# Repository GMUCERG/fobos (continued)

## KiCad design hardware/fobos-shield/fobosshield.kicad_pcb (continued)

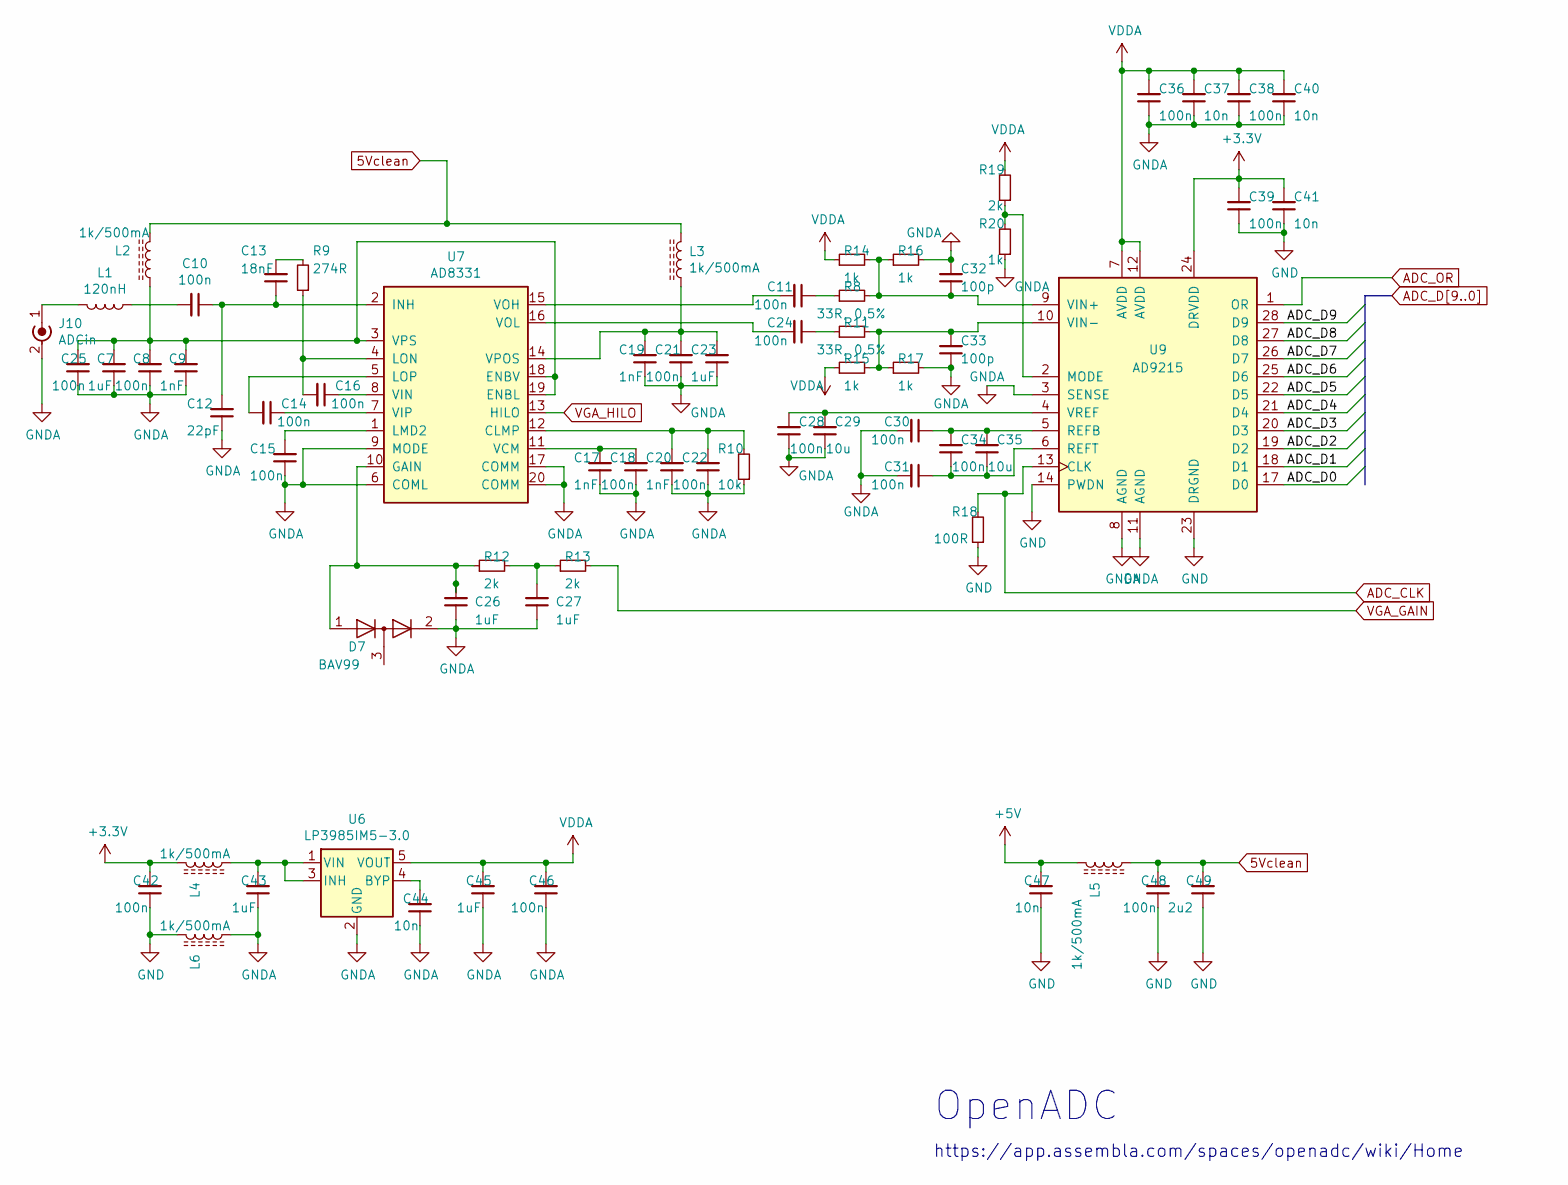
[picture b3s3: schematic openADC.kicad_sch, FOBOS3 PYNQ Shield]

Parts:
C7, C23, C26, C27, C43, C45: 1uF; C_0603_1608Metric
C8, C10, C11, C14, C15, C16, C18, C21, C22, C24, C25, C28, C30, C31, C34, C36, C38, C39, C42, C46, C48: 100n; C_0603_1608Metric
C9, C17, C19, C20: 1nF; C_0603_1608Metric
C12: 22pF; C_0603_1608Metric
C13: 18nF; C_0603_1608Metric
C29, C35: 10u; C_0603_1608Metric
C32, C33: 100p; C_0603_1608Metric
C37, C40, C41, C44, C47: 10n; C_0603_1608Metric
C49: 2u2; C_0603_1608Metric
D7: BAV99; SOT-23
J10: ADCin; SMA-JOHNSON-142-0701-801
L1: 120nH; L_0402_1005Metric
L2, L3, L4, L5, L6: 1k/500mA; L_0603_1608Metric
R8, R11: 33R, 0.5%; R_0603_1608Metric
R9: 274R; R_0603_1608Metric
R10: 10k; R_0603_1608Metric
R12, R13, R19: 2k; R_0603_1608Metric
R14, R15, R16, R17, R20: 1k; R_0603_1608Metric
R18: 100R; R_0603_1608Metric
U6: LP3985IM5-3.0; TSOT-23-5
U7: AD8331; QSOP-20_3.9x8.7mm_P0.635mm
U9: AD9215; TSSOP-28_4.4x9.7mm_P0.65mm

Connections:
5Vclean: C48.2, C49.2, L2.2, L3.2, L5.1
ADC_CLK: R18.2, U9.13 (CLK); also elsewhere on the board
ADC_D0: U9.17 (D0); also elsewhere on the board
ADC_D1: U9.18 (D1); also elsewhere on the board
ADC_D2: U9.19 (D2); also elsewhere on the board
ADC_D3: U9.20 (D3); also elsewhere on the board
ADC_D4: U9.21 (D4); also elsewhere on the board
ADC_D5: U9.22 (D5); also elsewhere on the board
ADC_D6: U9.25 (D6); also elsewhere on the board
ADC_D7: U9.26 (D7); also elsewhere on the board
ADC_D8: U9.27 (D8); also elsewhere on the board
ADC_D9: U9.28 (D9); also elsewhere on the board
ADC_OR: U9.1 (OR); also elsewhere on the board
GND: C39.1, C41.1, C42.1, C47.1, C48.1, C49.1, L6.2, R18.1, U9.14 (PWDN), U9.23 (DRGND); also elsewhere on the board
GNDA: C7.1, C8.1, C9.1, C12.1, C15.1, C17.1, C18.1, C19.1, C20.1, C21.1, C22.1, C23.1, C25.1, C26.1, C27.1, C28.1, C29.1, C30.2, C31.2, C32.2, C33.1, C36.1, C37.1, C38.1, C40.1, C43.1, C44.1, C45.1, C46.1, D7.2 (A), J10.2 (Ext), L6.1, R10.1, R16.2, R17.2, R20.1, U6.2 (GND), U7.6 (COML), U7.9 (MODE), U7.17 (COMM), U7.20 (COMM), U9.3 (SENSE), U9.8 (AGND), U9.11 (AGND)
unnamed: C10.1, C12.2, C13.1, U7.2 (INH)
unnamed: C10.2, L1.1
unnamed: C11.1, R8.1
unnamed: C11.2, U7.15 (VOH)
unnamed: C13.2, R9.2
unnamed: C14.1, U7.7 (VIP)
unnamed: C14.2, U7.5 (LOP)
unnamed: C15.2, U7.1 (LMD2)
unnamed: C16.1, U7.8 (VIN)
unnamed: C16.2, R9.1, U7.4 (LON)
unnamed: C17.2, C18.2, U7.11 (VCM)
unnamed: C19.2, C21.2, C23.2, L3.1, U7.14 (VPOS)
unnamed: C20.2, C22.2, R10.2, U7.12 (CLMP)
unnamed: C24.1, R11.1
unnamed: C24.2, U7.16 (VOL)
unnamed: C7.2, C8.2, C9.2, C25.2, L2.1, U7.3 (VPS), U7.18 (ENBV), U7.19 (ENBL)
unnamed: C26.2, D7.1 (K), R12.1, U7.10 (GAIN)
unnamed: C27.2, R12.2, R13.1
unnamed: C28.2, C29.2, U9.4 (VREF)
unnamed: C30.1, C34.2, C35.2, U9.5 (REFB)
unnamed: C31.1, C34.1, C35.1, U9.6 (REFT)
unnamed: C32.1, R8.2, R14.2, R16.1, U9.9 (VIN+)
unnamed: C33.2, R11.2, R15.2, R17.1, U9.10 (VIN-)
unnamed: C43.2, L4.1, U6.1 (VIN), U6.3 (INH)
unnamed: C44.2, U6.4 (BYP)
unnamed: J10.1 (In), L1.2
unnamed: R19.1, R20.2, U9.2 (MODE)
VCC3V3: C39.2, C41.2, C42.2, L4.2, U9.24 (DRVDD); also elsewhere on the board
VCC5V0: C47.2, L5.2; also elsewhere on the board
VDDA: C36.2, C37.2, C38.2, C40.2, C45.2, C46.2, R14.1, R15.1, R19.2, U6.5 (VOUT), U9.7 (AVDD), U9.12 (AVDD)
VGA_GAIN: R13.2; also elsewhere on the board
VGA_HILO: U7.13 (HILO); also elsewhere on the board

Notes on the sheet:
OpenADC
https://app.assembla.com/spaces/openadc/wiki/Home

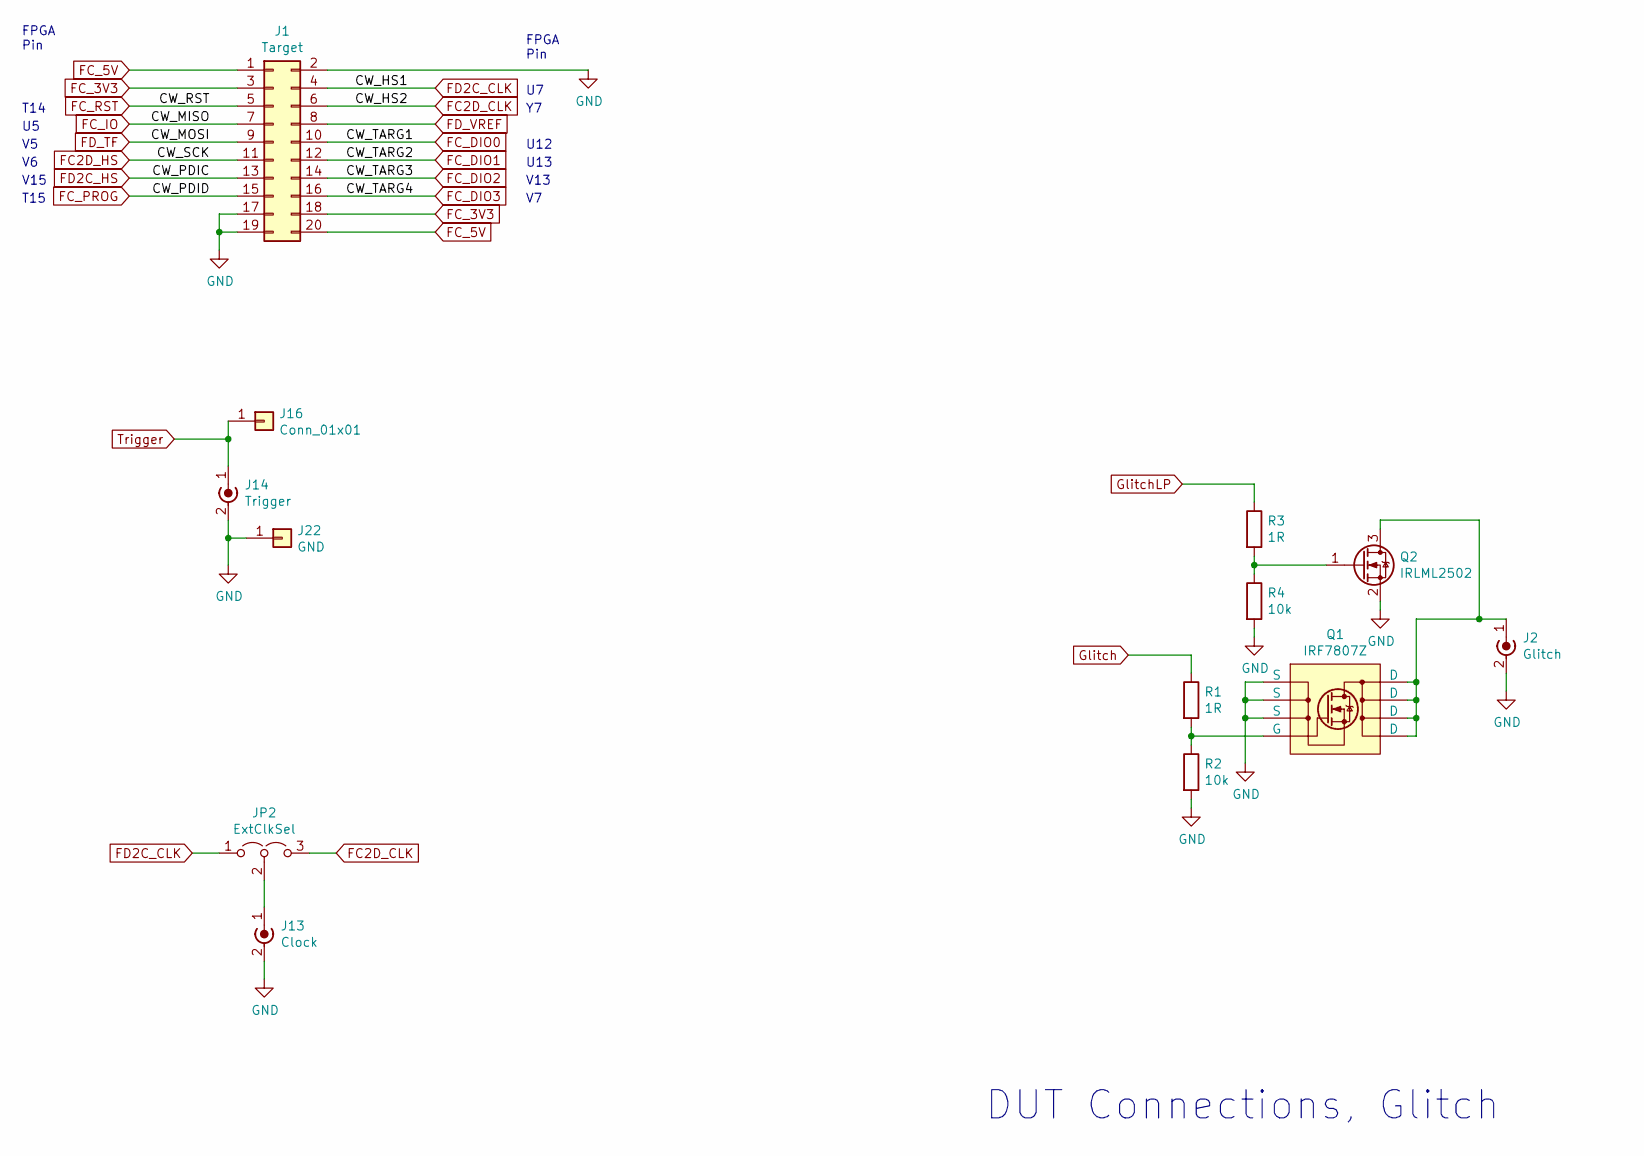
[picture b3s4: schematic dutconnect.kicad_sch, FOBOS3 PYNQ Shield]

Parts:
J1: Target; IDC-Header_2x10_P2.54mm_Horizontal
J2: Glitch; SMA-JOHNSON-142-0701-801
J13: Clock; SMA-JOHNSON-142-0701-801
J14: Trigger; SMA-JOHNSON-142-0701-801
J16: Conn_01x01; TestPoint_Loop_D2.60mm_Drill1.6mm_Beaded
J22: GND; TestPoint_Loop_D2.60mm_Drill1.6mm_Beaded
JP2: ExtClkSel; PinHeader_1x03_P2.54mm_Vertical
Q1: IRF7807Z; SOIC-8_3.9x4.9mm_P1.27mm
Q2: IRLML2502; SOT-23
R1, R3: 1R; R_0603_1608Metric
R2, R4: 10k; R_0603_1608Metric

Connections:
FC2D_CLK: J1.6, JP2.3 (B); also elsewhere on the board
FC2D_HS: J1.11; also elsewhere on the board
FC_3V3: J1.3, J1.18; also elsewhere on the board
FC_5V: J1.1, J1.20; also elsewhere on the board
FC_DIO0: J1.10; also elsewhere on the board
FC_DIO1: J1.12; also elsewhere on the board
FC_DIO2: J1.14; also elsewhere on the board
FC_DIO3: J1.16; also elsewhere on the board
FC_IO: J1.7; also elsewhere on the board
FC_PROG: J1.15; also elsewhere on the board
FC_RST: J1.5; also elsewhere on the board
FD2C_CLK: J1.4, JP2.1 (A); also elsewhere on the board
FD2C_HS: J1.13; also elsewhere on the board
FD_TF: J1.9; also elsewhere on the board
FD_VREF: J1.8
GND: J1.2, J1.17, J1.19, J2.2 (Ext), J13.2 (Ext), J14.2 (Ext), J22.1, Q1.1 (S), Q1.2 (S), Q1.3 (S), Q2.2 (S), R2.2, R4.2; also elsewhere on the board
Glitch: R1.1; also elsewhere on the board
GlitchLP: R3.1; also elsewhere on the board
unnamed: J2.1 (In), Q1.5 (D), Q1.6 (D), Q1.7 (D), Q1.8 (D), Q2.3 (D)
unnamed: J13.1 (In), JP2.2 (C)
unnamed: Q1.4 (G), R1.2, R2.1
unnamed: Q2.1 (G), R3.2, R4.1
Trigger: J14.1 (In), J16.1; also elsewhere on the board

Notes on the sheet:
V15
V13
T14
DUT Connections, Glitch
U12
T15
FPGA Pin
U13

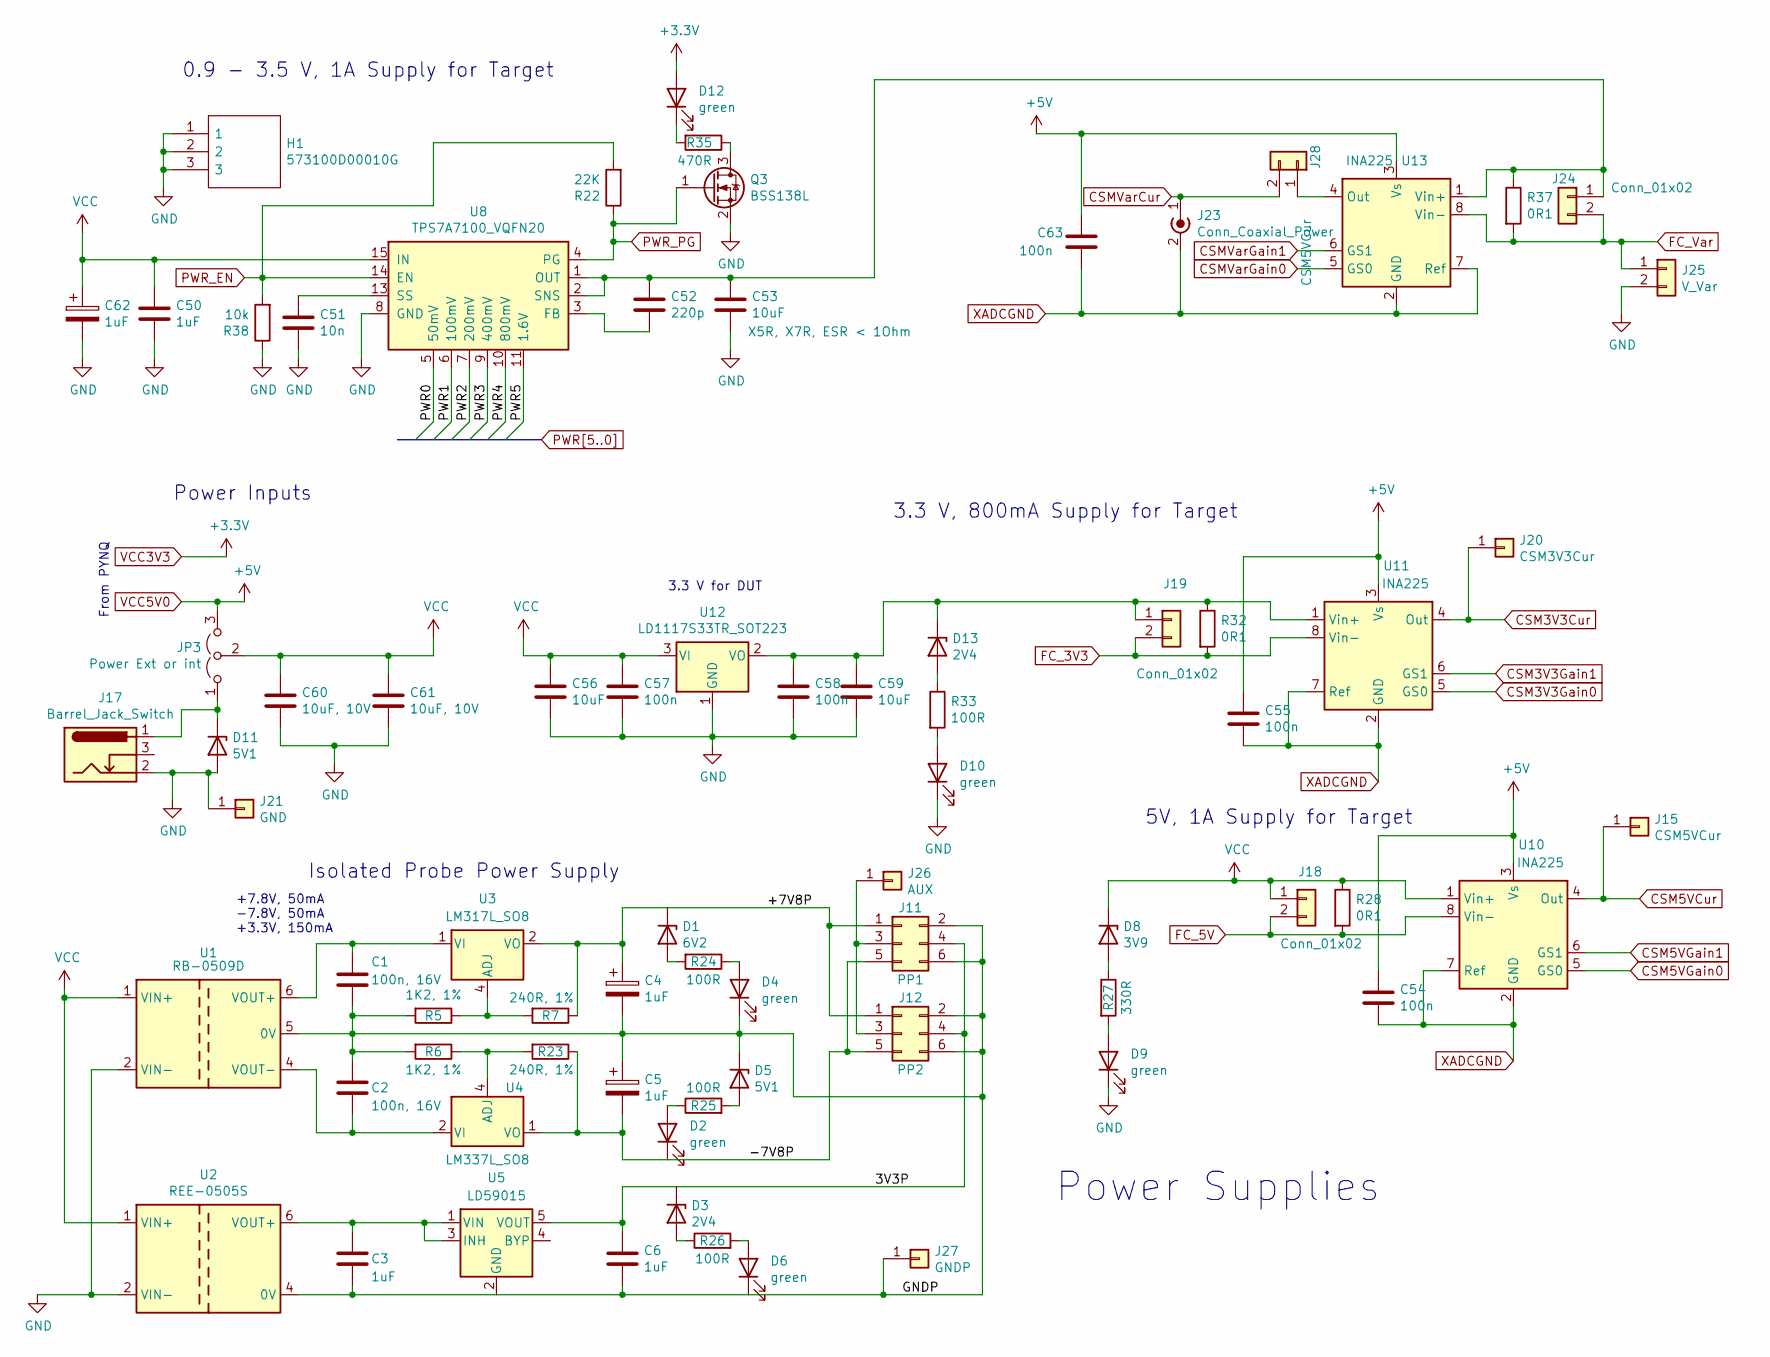
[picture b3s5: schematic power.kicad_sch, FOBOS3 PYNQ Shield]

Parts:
C1, C2: 100n, 16V; C_0603_1608Metric
C3, C6, C50: 1uF; C_0603_1608Metric
C4, C5, C62: 1uF; CP_EIA-3216-18_Kemet-A
C51: 10n; C_0402_1005Metric
C52: 220p; C_0402_1005Metric
C53, C56, C59: 10uF; C_0805_2012Metric
C54, C55, C57, C58, C63: 100n; C_0603_1608Metric
C60, C61: 10uF, 10V; C_0805_2012Metric
D1: 6V2; D_SOT-23_ANK
D2, D4, D6, D9, D10, D12: green; LED_0603_1608Metric
D3, D13: 2V4; D_SOT-23_ANK
D5, D11: 5V1; D_SOT-23_ANK
D8: 3V9; D_SOT-23_ANK
H1: 573100D00010G; Mouser Part Number 532-573100D00010G
J11: PP1; IDC-Header_2x03_P2.54mm_Horizontal
J12: PP2; IDC-Header_2x03_P2.54mm_Horizontal
J15: CSM5VCur; PinHeader_1x01_P2.54mm_Vertical
J17: Barrel_Jack_Switch; BarrelJack_CUI_PJ-102AH_Horizontal
J18, J19, J24: Conn_01x02; PinHeader_1x02_P2.54mm_Vertical
J20: CSM3V3Cur; PinHeader_1x01_P2.54mm_Vertical
J21: GND; PinHeader_1x01_P2.54mm_Vertical
J23: Conn_Coaxial_Power; SMA_Amphenol_901-144_Vertical
J25: V_Var; Molex_KK-254_AE-6410-02A_1x02_P2.54mm_Vertical
J26: AUX; PinHeader_1x01_P2.54mm_Vertical
J27: GNDP; PinHeader_1x01_P2.54mm_Vertical
J28: CSM5VCur; PinHeader_1x02_P2.54mm_Vertical
JP3: Power Ext or int; PinHeader_1x03_P2.54mm_Vertical
Q3: BSS138L; SOT-23
R5, R6: 1K2, 1%; R_0603_1608Metric
R7, R23: 240R, 1%; R_0603_1608Metric
R22: 22K; R_0603_1608Metric
R24, R25, R26, R33: 100R; R_0603_1608Metric
R27: 330R; R_0603_1608Metric
R28, R32, R37: 0R1; R_1206_3216Metric
R35: 470R; R_0603_1608Metric
R38: 10k; R_0603_1608Metric
U1: RB-0509D; Converter_DCDC_muRata_NMAxxxxSC_THT
U2: REE-0505S; Converter_DCDC_muRata_NMAxxxxSC_THT
U3: LM317L_SO8; SOIC-8_3.9x4.9mm_P1.27mm
U4: LM337L_SO8; SOIC-8_3.9x4.9mm_P1.27mm
U5: LD59015; TSOT-23-5
U8: TPS7A7100_VQFN20; Texas_VQFN-RGW-20
U10, U11, U13: INA225; MSOP-8_3x3mm_P0.65mm
U12: LD1117S33TR_SOT223; SOT-223-3_TabPin2

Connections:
/Power/3V3P: C6.1, D3.1 (K), J11.4, J12.4, U5.5 (VOUT)
/Power/+7V8P: C4.1, D1.1 (K), J11.1, J12.1, R7.1, U3.2 (VO), U3.3 (VO), U3.6 (VO), U3.7 (VO)
/Power/-7V8P: C5.2, D2.1 (K), J11.5, J12.5, R23.1, U4.1 (VO)
/Power/GNDP: C1.2, C2.1, C3.2, C4.2, C5.1, C6.2, D4.1 (K), D5.1 (K), D6.1 (K), J11.2, J11.6, J12.2, J12.6, J27.1, R5.2, R6.2, U1.5 (0V), U2.4 (0V), U5.2 (GND)
CSM3V3Cur: J20.1, U11.4 (Out); also elsewhere on the board
CSM3V3Gain0: U11.5 (GS0); also elsewhere on the board
CSM3V3Gain1: U11.6 (GS1); also elsewhere on the board
CSM5VCur: J15.1, U10.4 (Out); also elsewhere on the board
CSM5VGain0: U10.5 (GS0); also elsewhere on the board
CSM5VGain1: U10.6 (GS1); also elsewhere on the board
CSMVarCur: J23.1 (In), J28.2; also elsewhere on the board
CSMVarGain0: U13.5 (GS0); also elsewhere on the board
CSMVarGain1: U13.6 (GS1); also elsewhere on the board
FC_3V3: J19.2, R32.2, U11.8 (Vin-); also elsewhere on the board
FC_5V: J18.2, R28.2, U10.8 (Vin-); also elsewhere on the board
FC_Var: J24.2, J25.1, R37.2, U13.8 (Vin-); also elsewhere on the board
GND: C50.2, C51.2, C53.2, C56.2, C57.2, C58.2, C59.2, C60.2, C61.2, C62.2, D9.1 (K), D10.1 (K), D11.2 (A), H1.1, H1.2, H1.3, J17.2, J21.1, J25.2, Q3.2 (S), R38.1, U1.2 (VIN-), U2.2 (VIN-), U8.8 (GND), U8.12 (GND), U8.18 (GND), U8.21 (GND), U12.1 (GND); also elsewhere on the board
IN: C50.1, C56.1, C57.1, C60.1, C61.1, C62.1, D8.1 (K), J18.1, JP3.2 (C), R28.1, U1.1 (VIN+), U2.1 (VIN+), U8.15 (IN), U8.16 (IN), U8.17 (IN), U10.1 (Vin+), U12.3 (VI)
unnamed: C1.1, U1.6 (VOUT+), U3.1 (VI)
unnamed: C2.2, U1.4 (VOUT-), U4.2 (VI), U4.3 (VI), U4.6 (VI), U4.7 (VI)
unnamed: C3.1, U2.6 (VOUT+), U5.1 (VIN), U5.3 (INH)
unnamed: C51.1, U8.13 (SS)
unnamed: C52.1, C53.1, J24.1, R37.1, U8.1 (OUT), U8.2 (SNS), U8.19 (OUT), U8.20 (OUT), U13.1 (Vin+)
unnamed: C52.2, U8.3 (FB)
unnamed: C58.1, C59.1, D13.1 (K), J19.1, R32.1, U11.1 (Vin+), U12.2 (VO)
unnamed: D1.2 (A), R24.2
unnamed: D2.2 (A), R25.1
unnamed: D3.2 (A), R26.1
unnamed: D4.2 (A), R24.1
unnamed: D5.2 (A), R25.2
unnamed: D6.2 (A), R26.2
unnamed: D8.2 (A), R27.1
unnamed: D9.2 (A), R27.2
unnamed: D10.2 (A), R33.2
unnamed: D11.1 (K), J17.1, JP3.1 (A)
unnamed: D12.1 (K), R35.2
unnamed: D13.2 (A), R33.1
unnamed: J11.3, J12.3, J26.1
unnamed: J28.1, U13.4 (Out)
unnamed: Q3.3 (D), R35.1
unnamed: R5.1, R7.2, U3.4 (ADJ)
unnamed: R6.1, R23.2, U4.4 (ADJ)
PWR0: U8.5 (50mV); also elsewhere on the board
PWR1: U8.6 (100mV); also elsewhere on the board
PWR2: U8.7 (200mV); also elsewhere on the board
PWR3: U8.9 (400mV); also elsewhere on the board
PWR4: U8.10 (800mV); also elsewhere on the board
PWR5: U8.11 (1.6V); also elsewhere on the board
PWR_EN: R22.2, R38.2, U8.14 (EN); also elsewhere on the board
PWR_PG: Q3.1 (G), R22.1, U8.4 (PG); also elsewhere on the board
VCC3V3: D12.2 (A); also elsewhere on the board
VCC5V0: C54.1, C55.1, C63.1, JP3.3 (B), U10.3 (Vs), U11.3 (Vs), U13.3 (Vs); also elsewhere on the board
XADCGND: C54.2, C55.2, C63.2, J23.2 (Ext), U10.2 (GND), U10.7 (Ref), U11.2 (GND), U11.7 (Ref), U13.2 (GND), U13.7 (Ref); also elsewhere on the board

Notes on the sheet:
+7.8V, 50mA -7.8V, 50mA +3.3V, 150mA
Power Inputs
5V, 1A Supply for Target
3.3 V for DUT
Power Supplies
From PYNQ
0.9 - 3.5 V, 1A Supply for Target
Isolated Probe Power Supply
3.3 V, 800mA Supply for Target

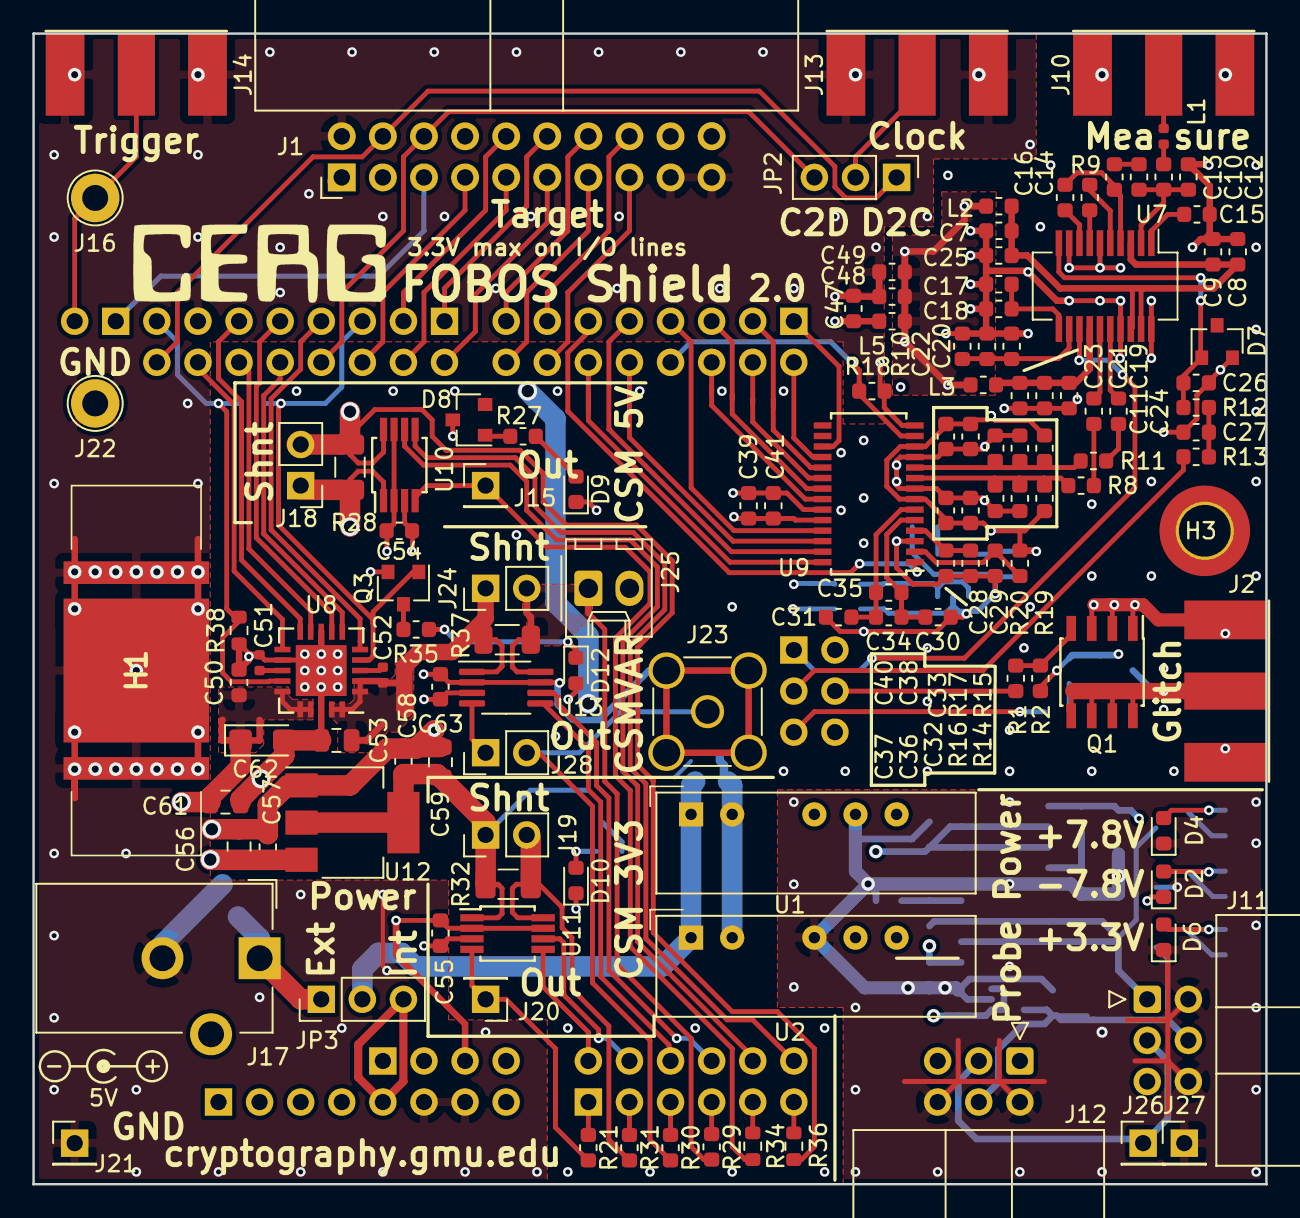
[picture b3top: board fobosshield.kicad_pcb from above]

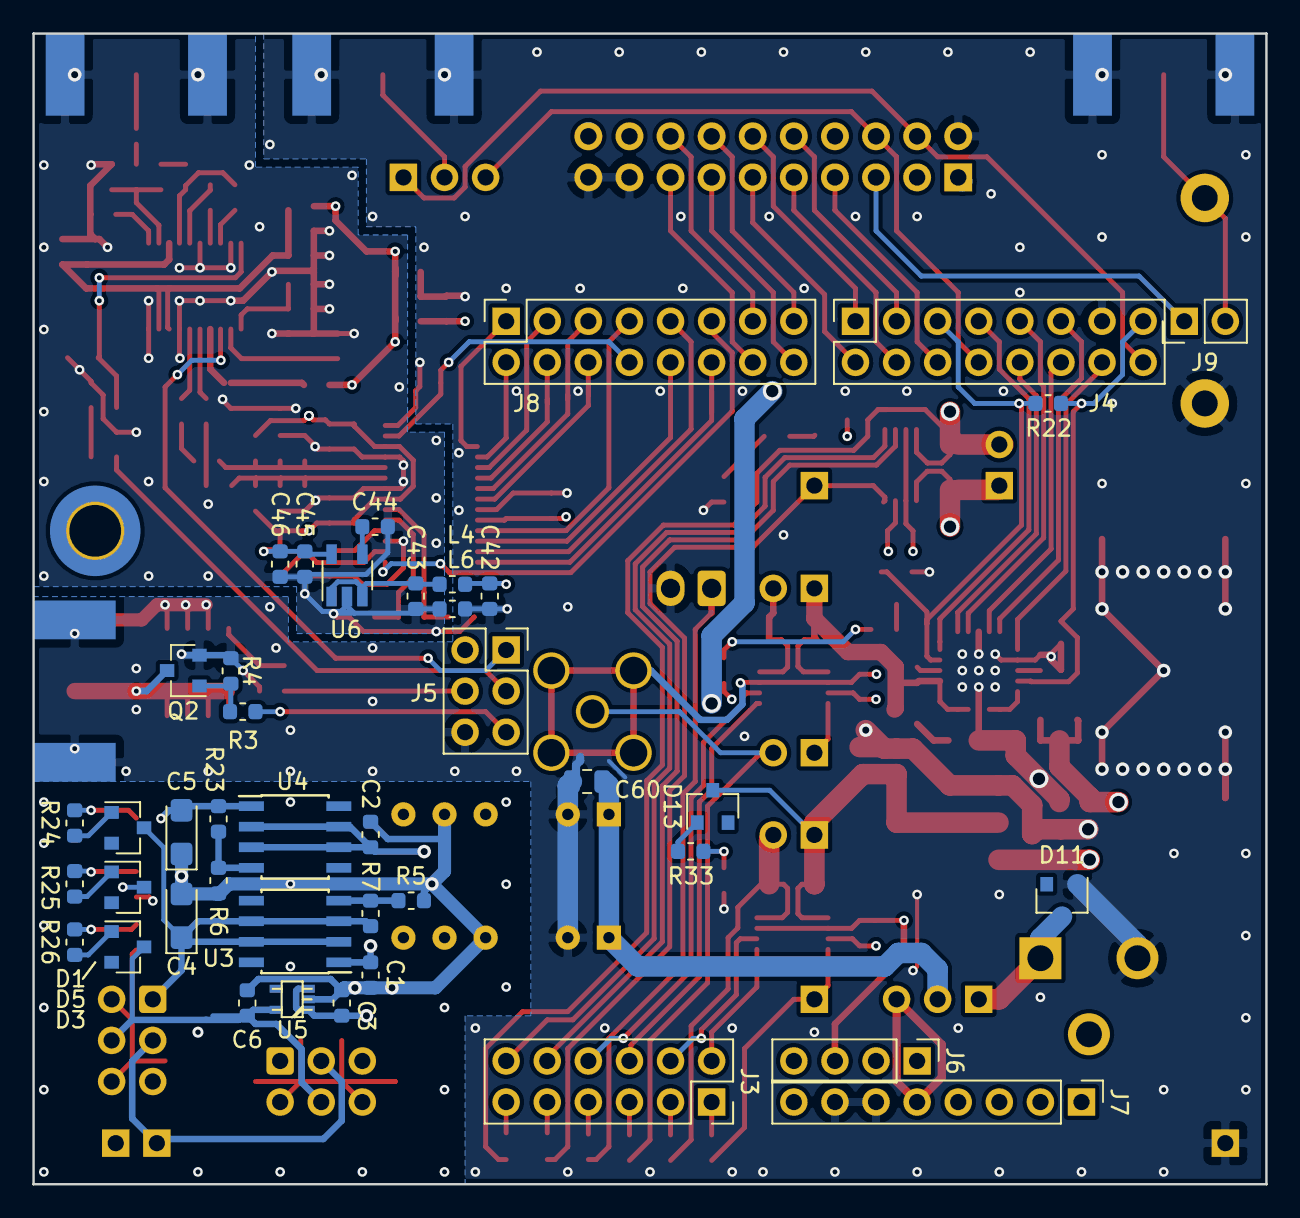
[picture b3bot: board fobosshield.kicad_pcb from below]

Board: 4 copper layers, 76.2 x 71.1 mm, 168 parts (42 on the bottom side), 122 nets.

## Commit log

2023-11-30 import from development
2023-12-08 fixing XILINX_XRT problem
2024-01-23 added ADC HiLo setting
2024-01-26 install creates link for pynq_drivers
2024-01-26 Makefile can build overlay for all shields, some xdc files fixed
2024-02-13 fixed install script not detecting BOARD
2024-02-13 cleaner solution to BOARD problem
2024-03-13 added ADC doc
2024-03-21 updated some documentation
2024-03-22 working in DUT description
2024-03-25 DUT section restructured
2024-03-27 started AES description
2024-03-28 almost completed AES example description
2024-03-29 AES example description done
2024-04-11 Ascon DUT description
2024-04-18 clarification
2024-05-18 bugfix: pynq_z1_rev1 hangs with updated pynq_z1_rev1.xdc. Updated Makefile to use ctrl_top_wrapper_shield_v1.vhd
2024-05-25 reverted changes in the previous commit
2024-06-04 started tvgen fix
2024-06-06 fobosTVGen can now accept AD and nonce
2024-06-10 restructuring TVGEN documentation, checking serial for MTC
2024-06-18 test vector documentation update
2024-06-19 Updated cpa.py with intersection calculations
2024-06-19 added missing kicad project files
2024-06-21 Updated CERG Copyright, misc. comments removed
2024-07-01 new configuration folder on pynq
2024-07-01 fixed basic aes capture adc example
2024-07-02 small fix
2024-07-03 update lwc tools
2024-07-04 updated READMEs and documentation
2024-07-04 typo in README.md
2024-07-04 MTD output in correct directory
2024-08-16 new MTC pictures, many small fixes to pynqctrl for power commands
2024-08-16 pynq side fixes for fobos dut protocol error checking errors
2024-08-16 working pynclocal, removed changes from last commit
2024-09-09 smaller version of MSP430-label figures
2024-09-25 fixed MTD bug and MTD file output
2024-09-25 commented shape print statement
2024-09-25 changed show to no
2024-11-19 tested lock, unlock and status
2024-11-19 added online/offline status to host.show_instances
2024-11-23 improved locking code
2024-12-21 added set_uid command
2024-12-22 wip: adding host.connect method
2024-12-28 added host.disconnect method
2025-02-08 added target classes
2025-02-18 fixed a few issues with locking
2025-05-19 fixed typo
2025-05-27 MTD graph index fixed. MTD CSV fixed
2025-06-02 notes on clean installation on Kubuntu 24.04
2025-06-02 using xc3sprog for programming xilinx jtag
2025-06-02 Digilent Adept now supported
2025-06-04 added TVLA code from old fobos and inlcuded Ben's latest fixes on this branch
2025-06-05 increased param size to 5 so that larger userids work
2025-06-05 increased param to 5 for 5 digit userids
2025-06-06 updated sca labs to work with admin server
2025-06-24 updated basic notebooks
2025-09-11 intel/altera programing using quartus
2025-11-05 added info on how to build FOBOS Shield and updated BOM for Z1
2025-11-05 BOM now also for Shield Z2
2025-11-19 cleaned up FBDA7 rev1 added BOM, fixed bugs in schematic
